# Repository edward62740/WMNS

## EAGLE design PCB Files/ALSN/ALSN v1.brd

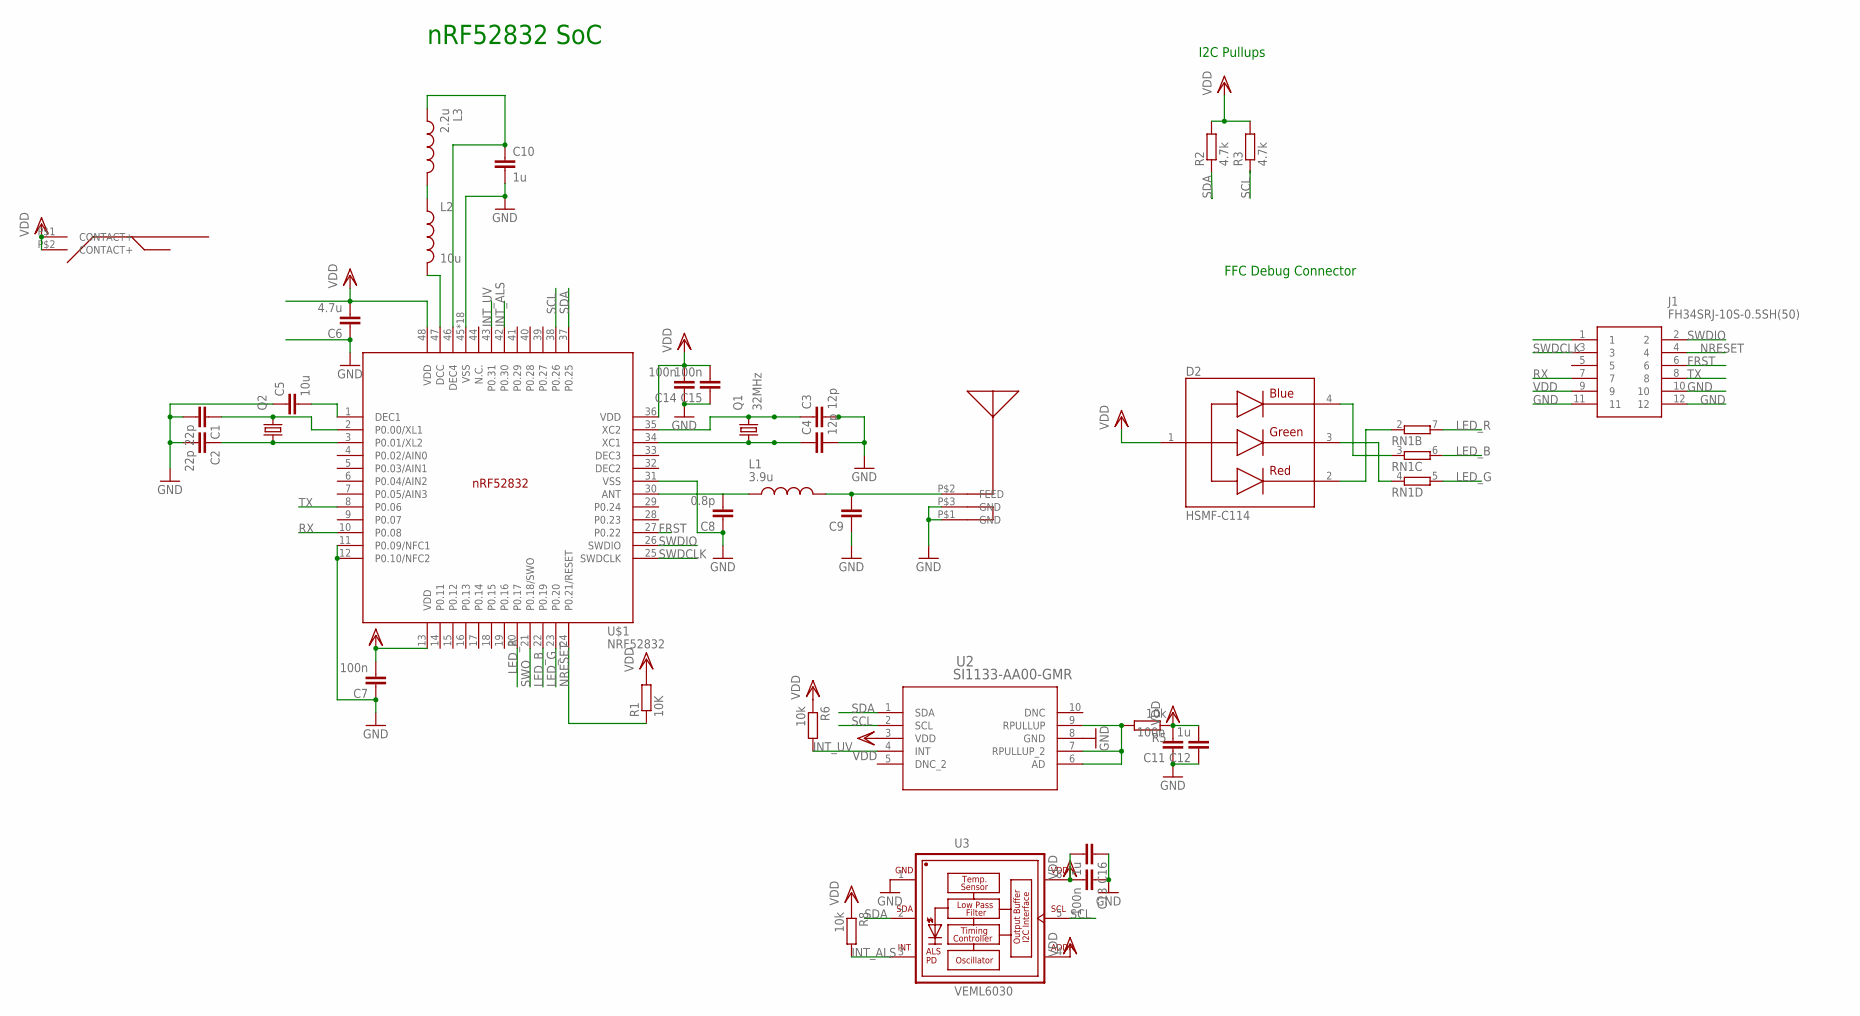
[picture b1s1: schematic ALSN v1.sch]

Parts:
C1, C2: 22p; C0402
C3, C4: 12p; C0402
C5: 10u; C0402
C6: 4.7u; C0402
C7: 100n; C0603R
C8: 0.8p; C0402
C9: 1.2p; C0402
C10, C12, C16: 1u; C0402
C11, C13, C14, C15: 100n; C0402
D2: HSMF-C114; DIOSC160X150X35-4N
J1: FH34SRJ-10S-0.5SH(50); FH34SRJ10S05SH50
L1: 3.9u; INDC0402X26N
L2: 10u; L0603
L3: 2.2u; INDC0402X26N
Q1: 32MHz; 2.0X1.6_KX-5
Q2: KX-327-RT; 2.0X1.2
R1: 10K; R0402
R2, R3: 4.7k; R0402
R5, R6, R8: 10k; R0402
RN1: 4R-N0402ARV341; 4X0402ARV341
U2: SI1133-AA00-GMR; 10QFN_2X2_SIL
U3: VEML6030; VISHAY_VEML6030_2X2X0.87
U$1: NRF52832; QFN40P600X600X90-48_N
U$2: CR2032-THT
U$4: CHIPANTENNAL2

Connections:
FRST: J1.6, U$1.27 (P0.22)
GND: C1.2, C2.2, C3.2, C4.2, C5.1, C6.1, C7.1, C8.1, C9.1, C10.2, C11.1, C12.1, C13.1, C14.1, C15.1, C16.1, J1.10, J1.11, J1.12, U2.8 (GND), U3.1 (GND), U$1.11 (P0.09/NFC1), U$1.12 (P0.10/NFC2), U$1.31 (VSS), U$1.45 (VSS), U$1.PAD (VSS), U$1.PAD@VIA01 (VSS), U$1.PAD@VIA02 (VSS), U$1.PAD@VIA03 (VSS), U$1.PAD@VIA04 (VSS), U$1.PAD@VIA05 (VSS), U$1.PAD@VIA06 (VSS), U$1.PAD@VIA07 (VSS), U$1.PAD@VIA08 (VSS), U$1.PAD@VIA09 (VSS), U$1.PAD@VIA10 (VSS), U$1.PAD@VIA11 (VSS), U$1.PAD@VIA12 (VSS), U$1.PAD@VIA13 (VSS), U$1.PAD@VIA14 (VSS), U$1.PAD@VIA15 (VSS), U$1.PAD@VIA16 (VSS), U$4.P$1 (GND), U$4.P$3 (GND)
INT_ALS: R8.2, U3.3 (INT), U$1.42 (P0.30)
INT_UV: R6.2, U2.4 (INT), U$1.43 (P0.31)
LED_B: RN1.6 (2), U$1.22 (P0.19)
LED_G: RN1.5 (2), U$1.23 (P0.20)
LED_R: RN1.7 (2), U$1.20 (P0.17)
unnamed: C1.1, Q2.2, U$1.2 (P0.00/XL1)
unnamed: C2.1, Q2.1, U$1.3 (P0.01/XL2)
unnamed: C3.1, Q1.3 (2), U$1.35 (XC2)
unnamed: C4.1, Q1.1, U$1.34 (XC1)
unnamed: C5.2, U$1.1 (DEC1)
unnamed: C8.2, L1.1, U$1.30 (ANT)
unnamed: L2.2, U$1.47 (DCC)
unnamed: L2.1, L3.2
unnamed: C10.1, L3.1, U$1.46 (DEC4)
unnamed: D2.3, RN1.4 (1)
unnamed: R5.2, U2.6 (AD), U2.7 (RPULLUP_2), U2.9 (RPULLUP)
unnamed: D2.2, RN1.2 (1)
unnamed: D2.4, RN1.3 (1)
NRESET: J1.4, R1.1, U$1.24 (P0.21/RESET)
RF: C9.2, L1.2, U$4.P$2 (FEED)
RX: J1.7, U$1.10 (P0.08)
SCL: R3.1, U2.2 (SCL), U3.5 (SCL), U$1.38 (P0.26)
SDA: R2.1, U2.1 (SDA), U3.2 (SDA), U$1.37 (P0.25)
SWDCLK: J1.3, U$1.25 (SWDCLK)
SWDIO: J1.2, U$1.26 (SWDIO)
SWO: U$1.21 (P0.18/SWO)
TX: J1.8, U$1.8 (P0.06)
VDD: C6.2, C7.2, C11.2, C12.2, C13.2, C14.2, C15.2, C16.2, D2.1, J1.9, R1.2, R2.2, R3.2, R5.1, R6.1, R8.1, U2.3 (VDD), U3.4 (ADDR), U3.6 (VDD), U$1.13 (VDD), U$1.36 (VDD), U$1.48 (VDD), U$2.P$1, U$2.P$2

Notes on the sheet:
nRF52832 SoC
I2C Pullups
FFC Debug Connector

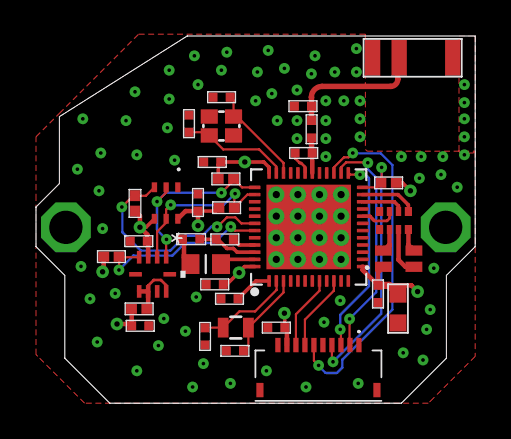
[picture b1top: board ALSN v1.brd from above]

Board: 4 copper layers, 24.4 x 20.4 mm, 35 parts (0 on the bottom side), 29 nets.

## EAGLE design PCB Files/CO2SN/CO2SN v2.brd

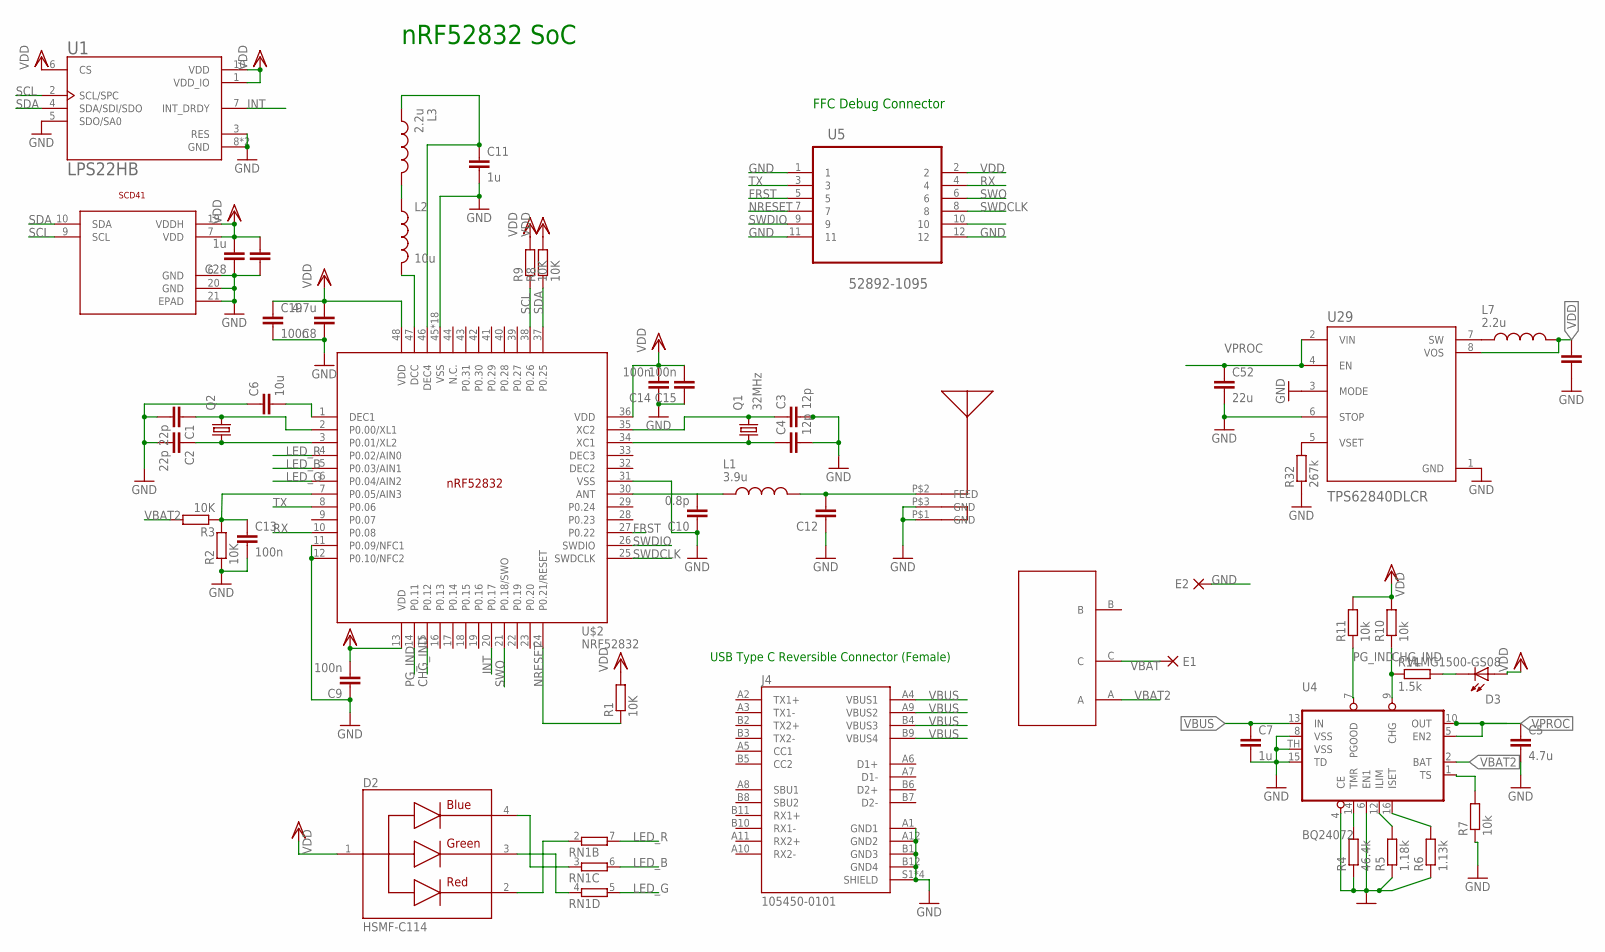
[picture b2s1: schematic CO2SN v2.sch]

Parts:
C1, C2: 22p; C0402
C3, C4: 12p; C0402
C5, C8: 4.7u; C0402
C6: 10u; C0402
C7, C11, C28: 1u; C0402
C9: 100n; C0603R
C10: 0.8p; C0402
C12: 1.2p; C0402
C13, C14, C15, C19: 100n; C0402
C29, C52, C58: 22u; C0603R
D2: HSMF-C114; DIOSC160X150X35-4N
D3: VLMG1500-GS08; LEDC1005X35N
E1, E2: DPADS_PAD-0400-S; DPADS_0400-S
J4: 105450-0101; MOLEX_105450-0101
L1: 3.9u; INDC0402X26N
L2: 10u; L0603
L3: 2.2u; INDC0402X26N
L7: 2.2u; INDC3225X120N
Q1: 32MHz; 2.0X1.6_KX-5
Q2: KX-327-RT; 2.0X1.2
R1, R2, R3, R8, R9: 10K; R0402
R4: 46.4k; R0402
R5: 1.18k; R0402
R6: 1.13k; R0402
R7, R10, R11: 10k; R0402
R14: 1.5k; R0402
R32: 267k; R0402
RN1: 4R-N0402ARV341; 4X0402ARV341
U1: LPS22HB; LGA10R50P2X3_200X200X80
U4: BQ24072; S-PVQFN-N16
U5: 52892-1095; MOLEX_52892-1095
U29: TPS62840DLCR; SON50P200X150X100-8N
U$1: SCD41
U$2: NRF52832; QFN40P600X600X90-48_N
U$3: SMDTOGGLESWITCH
U$4: CHIPANTENNAL2

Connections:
CHG_IND: R10.1, R14.1, U4.9 (CHG), U$2.15 (P0.12)
FRST: U5.5, U$2.27 (P0.22)
GND: C1.2, C2.2, C3.2, C4.2, C5.2, C6.1, C7.2, C8.1, C9.1, C10.1, C11.2, C12.1, C13.2, C14.1, C15.1, C19.2, C28.1, C29.2, C52.2, C58.2, E2.PAD, J4.A1 (GND1), J4.A12 (GND2), J4.B1 (GND3), J4.B12 (GND4), J4.S1 (SHIELD), J4.S2 (SHIELD), J4.S3 (SHIELD), J4.S4 (SHIELD), R2.1, R4.1, R5.1, R6.1, R7.1, R32.1, U1.3 (RES), U1.5 (SDO/SA0), U1.8 (GND), U1.9 (GND), U4.4 (CE), U4.6 (EN1), U4.8 (VSS), U4.15 (TD), U4.TH (VSS), U5.1, U5.11, U5.12, U29.1 (GND), U29.3 (MODE), U29.6 (STOP), U$1.6 (GND), U$1.20 (GND), U$1.21 (EPAD), U$2.11 (P0.09/NFC1), U$2.12 (P0.10/NFC2), U$2.31 (VSS), U$2.45 (VSS), U$2.PAD (VSS), U$2.PAD@VIA01 (VSS), U$2.PAD@VIA02 (VSS), U$2.PAD@VIA03 (VSS), U$2.PAD@VIA04 (VSS), U$2.PAD@VIA05 (VSS), U$2.PAD@VIA06 (VSS), U$2.PAD@VIA07 (VSS), U$2.PAD@VIA08 (VSS), U$2.PAD@VIA09 (VSS), U$2.PAD@VIA10 (VSS), U$2.PAD@VIA11 (VSS), U$2.PAD@VIA12 (VSS), U$2.PAD@VIA13 (VSS), U$2.PAD@VIA14 (VSS), U$2.PAD@VIA15 (VSS), U$2.PAD@VIA16 (VSS), U$4.P$1 (GND), U$4.P$3 (GND)
INT: U1.7 (INT_DRDY), U$2.20 (P0.17)
LED_B: RN1.6 (2), U$2.5 (P0.03/AIN1)
LED_G: RN1.5 (2), U$2.6 (P0.04/AIN2)
LED_R: RN1.7 (2), U$2.4 (P0.02/AIN0)
unnamed: C1.1, Q2.2, U$2.2 (P0.00/XL1)
unnamed: C2.1, Q2.1, U$2.3 (P0.01/XL2)
unnamed: C3.1, Q1.3 (2), U$2.35 (XC2)
unnamed: C4.1, Q1.1, U$2.34 (XC1)
unnamed: L2.2, U$2.47 (DCC)
unnamed: C10.2, L1.1, U$2.30 (ANT)
unnamed: C6.2, U$2.1 (DEC1)
unnamed: R4.2, U4.14 (TMR)
unnamed: R5.2, U4.12 (ILIM)
unnamed: L2.1, L3.2
unnamed: C11.1, L3.1, U$2.46 (DEC4)
unnamed: R6.2, U4.16 (ISET)
unnamed: D2.2, RN1.2 (1)
unnamed: D3.2, R14.2
unnamed: C13.1, R2.2, R3.1, U$2.7 (P0.05/AIN3)
unnamed: D2.3, RN1.4 (1)
unnamed: D2.4, RN1.3 (1)
unnamed: L7.1, U29.7 (SW)
unnamed: R32.2, U29.5 (VSET)
NRESET: R1.1, U5.7, U$2.24 (P0.21/RESET)
PG_IND: R11.1, U4.7 (PGOOD), U$2.14 (P0.11)
RF: C12.2, L1.2, U$4.P$2 (FEED)
RX: U5.4, U$2.10 (P0.08)
SCL: R9.1, U1.2 (SCL/SPC), U$1.9 (SCL), U$2.38 (P0.26)
SDA: R8.1, U1.4 (SDA/SDI/SDO), U$1.10 (SDA), U$2.37 (P0.25)
SWDCLK: U5.8, U$2.25 (SWDCLK)
SWDIO: U5.9, U$2.26 (SWDIO)
SWO: U5.6, U$2.21 (P0.18/SWO)
TS: R7.2, U4.1 (TS)
TX: U5.3, U$2.8 (P0.06)
VBAT: E1.PAD, U$3.C
VBAT2: R3.2, U4.2 (BAT), U$3.A
VBUS: C7.1, J4.A4 (VBUS1), J4.A9 (VBUS2), J4.B4 (VBUS3), J4.B9 (VBUS4), U4.13 (IN)
VDD: C8.2, C9.2, C14.2, C15.2, C19.1, C28.2, C29.1, C58.1, D2.1, D3.1, L7.2, R1.2, R8.2, R9.2, R10.2, R11.2, U1.1 (VDD_IO), U1.6 (CS), U1.10 (VDD), U5.2, U29.8 (VOS), U$1.7 (VDD), U$1.19 (VDDH), U$2.13 (VDD), U$2.36 (VDD), U$2.48 (VDD)
VPROC: C5.1, C52.1, U4.5 (EN2), U4.10 (OUT), U29.2 (VIN), U29.4 (EN)

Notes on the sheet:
nRF52832 SoC
USB Type C Reversible Connector (Female)
FFC Debug Connector

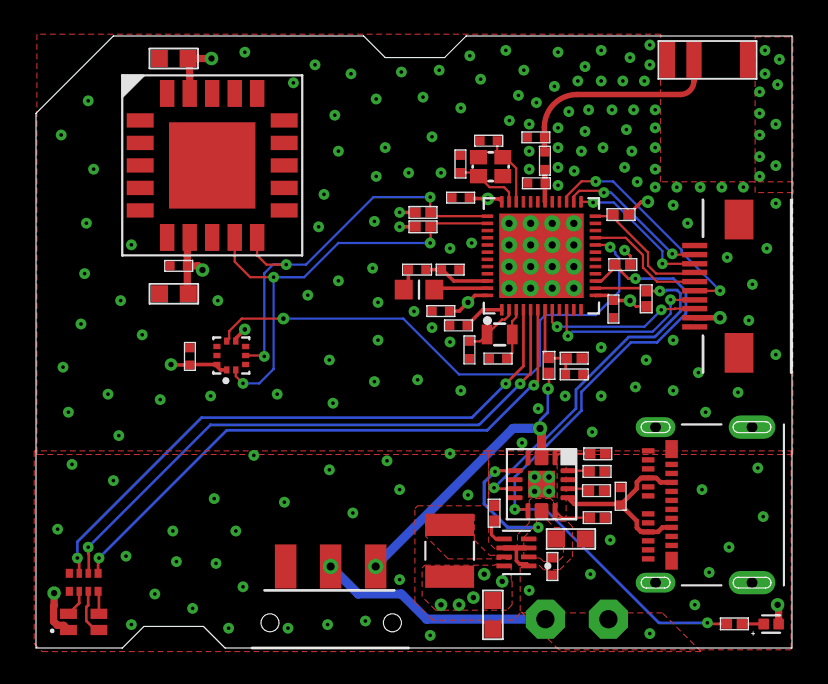
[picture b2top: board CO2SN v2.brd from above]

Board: 4 copper layers, 42.0 x 34.0 mm, 53 parts (0 on the bottom side), 42 nets.

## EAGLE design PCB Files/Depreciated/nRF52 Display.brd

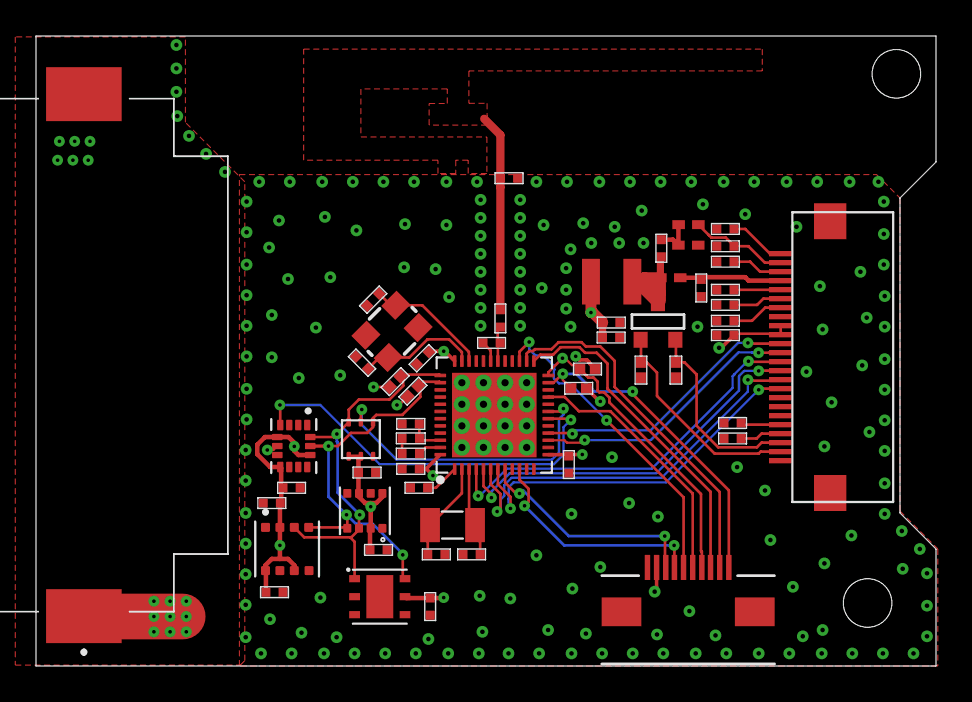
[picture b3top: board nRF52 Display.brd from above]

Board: 4 copper layers, 50.0 x 35.0 mm, 55 parts (0 on the bottom side), 43 nets.

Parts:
C1, C2: 12pF; C0402
C3, C4: 12p; C0402
C5: 10u; C0402
C6, C26, C27: 4.7u; C0402
C7, C11, C12, C13, C17, C30: 100n; C0402
C8: 0.8p; C0402
C9: 1.2p; C0402
C10, C15, C16, C18, C19, C20, C21, C22, C23, C24, C25, C28, C29: 1u; C0402
C14: 100u; C0402
D1, D2, D3: 1PS79SB30,115; SOD523
K1: 687124149022
L1: 3.9u; INDC0402X26N
L2: SM-NE29
L4: 10u; INDC0402X26N
L5: 15n; INDC0402X26N
R1, R4: 10K; R0402
R2, R3: 4.7k; R0402
R5: 10k; R0402
R6: 0.47; R0402
T1: SOT-23
U1: CR2032-BS-6-1; CR2032BS61
U2: BME280; PSON65P250X250X100-8N
U4: SHT20; DFN300X300X110-7N
U5: 52892-1095; MOLEX_52892-1095
U6: BME680; PSON80P300X300X100-8N
U7: BMI160; PQFN50P300X250X88-14N
U$1: NRF52832; QFN40P600X600X90-48_N
U$2: TI-OPT3001
X1: ABS07-32.768KHZ-T
Y1: CRYSTAL-26MHZSMD-3.2X2.5; CRYSTAL-SMD-3.2X2.5MM

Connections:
BUSY: K1.9, U$1.7
CS: K1.12, U$1.4
D/C: K1.11, U$1.5
DFU: R4.1, U5.10, U$1.23
FRST: U5.5, U$1.27
GDR: K1.2, R5.2, T1.3
GND: C1.2, C2.2, C3.2, C4.2, C5.1, C6.1, C7.1, C8.1, C9.1, C10.2, C11.1, C12.1, C13.1, C14.1, C15.1, C16.1, C17.2, C18.1, C19.1, C20.1, C21.1, C22.2, C23.1, C24.1, C25.1, C26.2, C28.2, C29.2, C30.2, D2.1, K1.8, K1.17, R5.1, R6.1, U1.2, U2.1, U2.5, U2.7, U4.2, U4.7, U5.1, U5.11, U5.12, U6.1, U6.5, U6.7, U7.1, U7.6, U7.7, U$1.11, U$1.12, U$1.31, U$1.45, U$1.PAD, U$1.PAD@VIA01, U$1.PAD@VIA02, U$1.PAD@VIA03, U$1.PAD@VIA04, U$1.PAD@VIA05, U$1.PAD@VIA06, U$1.PAD@VIA07, U$1.PAD@VIA08, U$1.PAD@VIA09, U$1.PAD@VIA10, U$1.PAD@VIA11, U$1.PAD@VIA12, U$1.PAD@VIA13, U$1.PAD@VIA14, U$1.PAD@VIA15, U$1.PAD@VIA16, U$2.3
INT_BMI: U7.4, U$1.18
INT_OPT: U$1.19, U$2.5
MOSI: K1.14, U$1.16
unnamed: C1.1, U$1.2, X1.2
unnamed: C2.1, U$1.3, X1.1
unnamed: C3.1, U$1.35, Y1.3
unnamed: C4.1, U$1.34, Y1.1
unnamed: C5.2, U$1.1
unnamed: C8.2, L1.1, U$1.30
unnamed: C27.2, D3.2, L2.2, T1.1
unnamed: C21.2, K1.18
unnamed: L4.2, U$1.47
unnamed: L4.1, L5.2
unnamed: C10.1, L5.1, U$1.46
unnamed: C18.2, K1.22
unnamed: C20.2, K1.19
unnamed: C19.2, K1.20
unnamed: C15.2, K1.24
unnamed: C24.2, K1.4
unnamed: C25.2, K1.5
unnamed: C27.1, D1.1, D2.2
NRESET: R1.1, U5.7, U$1.24
PREVGH: C22.1, D3.1, K1.21
PREVGL: C16.2, D1.2, K1.23
RES: K1.10, U$1.6
RESE: K1.3, R6.2, T1.2
RF: C9.2, L1.2
RX: U5.4, U$1.10
SCK: K1.13, U$1.15
SCL: R3.1, U2.4, U4.6, U6.4, U7.13, U$1.38, U$2.4
SDA: R2.1, U2.3, U4.1, U6.3, U7.14, U$1.37, U$2.6
SWDCLK: U5.8, U$1.25
SWDIO: U5.9, U$1.26
SWO: U5.6, U$1.21
TX: U5.3, U$1.8
VDD: C6.2, C7.2, C11.2, C12.2, C13.2, C14.2, C17.1, C23.2, C26.1, C28.1, C29.1, C30.1, K1.15, K1.16, L2.1, R1.2, R2.2, R3.2, R4.2, U1.1, U2.2, U2.6, U2.8, U4.5, U5.2, U6.2, U6.6, U6.8, U7.5, U7.8, U7.12, U$1.13, U$1.36, U$1.48, U$2.1, U$2.2

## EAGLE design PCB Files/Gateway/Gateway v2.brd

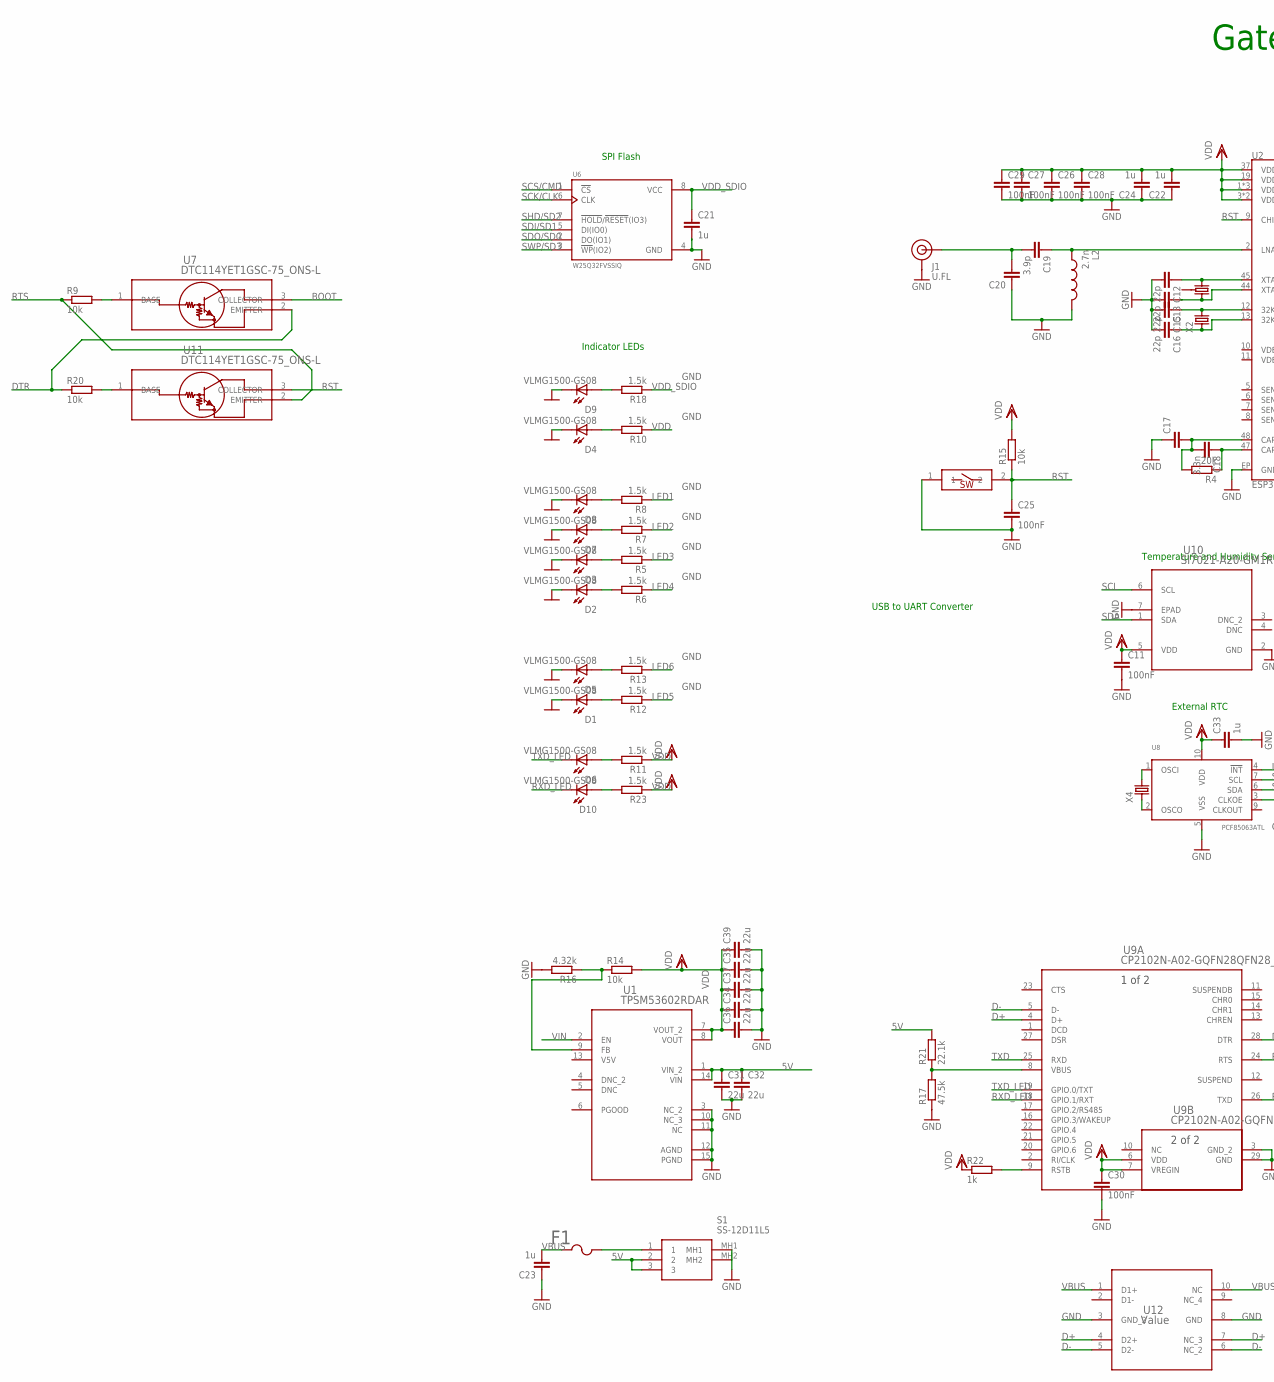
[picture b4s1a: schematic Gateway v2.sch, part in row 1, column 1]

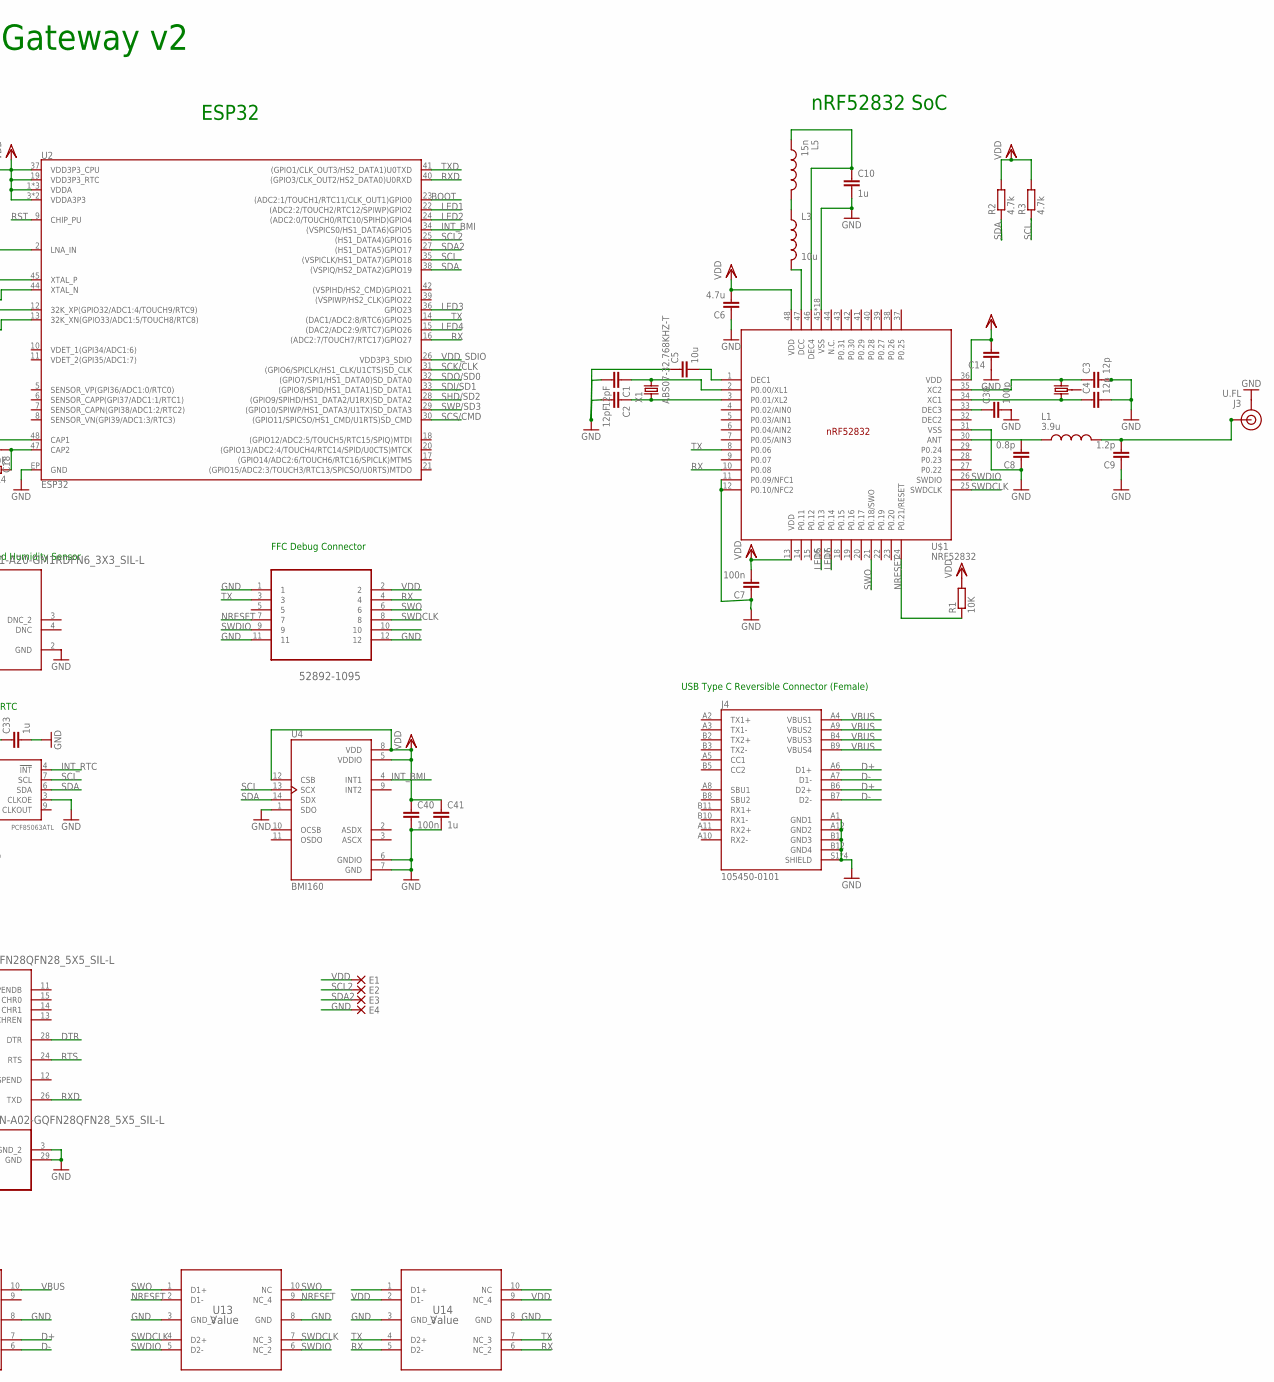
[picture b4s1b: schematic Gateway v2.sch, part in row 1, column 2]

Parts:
C1, C2: 12pF; C0402
C3, C4: 12p; C0402
C5: 10u; C0402
C6: 4.7u; C0402
C7, C40: 100n; C0402
C8: 0.8p; C0402
C9: 1.2p; C0402
C10, C21, C41: 1u; C0402
C11, C25, C26, C27, C28, C29, C30: 100nF; C0402
C12, C13, C15, C16: 22p; C0402
C14: 100u; C0402
C17: 10n; C0402
C18: 3.3n; C0402
C19: 3.9p; C0402
C20: 2.4p; C0402
C22, C23, C24, C33: 1u; C0603R
C31, C32, C34, C35, C36, C37, C39: 22u; C0603R
C38: 100p; C0402
D1, D2, D3, D4, D5, D6, D7, D8, D9, D10: VLMG1500-GS08; LEDC1005X35N
E1, E2, E3, E4: DPADS_PAD-0400-S; DPADS_0400-S
F1: 1210L050YR1210LSERIES_LTF-L; 1210LSERIES_LTF-L
J1, J3: U.FL
J4: 105450-0101; MOLEX_105450-0101
L1: 3.9u; INDC0402X26N
L2: 2.7n; INDC0402X26N
L3: 10u; L0603
L5: 15n; INDC0402X26N
R1: 10K; R0402
R2, R3: 4.7k; R0402
R4: 20k; R0402
R5, R6, R7, R8, R10, R11, R12, R13, R18, R23: 1.5k; R0402
R9, R14, R15, R20: 10k; R0402
R16: 4.32k; R0402
R17: 47.5k; R0402
R21: 22.1k; R0402
R22: 1k; R0402
RESET: SMDSWITCH; RESC4217X170
S1: SS-12D11L5; SS12D11L5
U1: TPSM53602RDAR; B3QFN15_RDA_TEX
U2: ESP32; QFN48-0.4MM
U4: BMI160; PQFN50P300X250X88-14N
U5: 52892-1095; MOLEX_52892-1095
U6: W25Q32FVSSIQ; SOIC127P790X216-8N
U7, U11: DTC114YET1GSC-75_ONS-L; SC-75_ONS-L
U8: PCF85063ATL; SOT1197-1
U9: CP2102N-A02-GQFN28QFN28_5X5_SIL-L; QFN28_5X5_SIL-L
U10: SI7021-A20-GM1RDFN6_3X3_SIL-L; DFN6_3X3_SIL-L
U12, U13, U14: Value; DQA0010A
U$1: NRF52832; QFN40P600X600X90-48_N
X1, X2, X4: ABS07-32.768KHZ-T
Y1, Y2: CRYSTAL-26MHZSMD-3.2X2.5; CRYSTAL-SMD-3.2X2.5MM

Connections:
5V: C31.1, C32.1, R21.2, S1.2, S1.3, U1.1 (VIN_2), U1.14 (VIN)
BOOT: U2.23 ((ADC2:1/TOUCH1/RTC11/CLK_OUT1)GPIO0), U7.3 (COLLECTOR)
D+: J4.A6 (D1+), J4.B6 (D2+), U9.4 (D+), U12.4 (D2+), U12.7 (NC_3)
D-: J4.A7 (D1-), J4.B7 (D2-), U9.5 (D-), U12.5 (D2-), U12.6 (NC_2)
DTR: R20.1, U7.2 (EMITTER), U9.28 (DTR)
GND: C1.2, C2.2, C3.2, C4.2, C5.1, C6.1, C7.1, C8.1, C9.1, C10.2, C11.2, C12.2, C13.2, C14.1, C15.2, C16.2, C17.1, C20.1, C21.2, C22.1, C23.1, C24.1, C25.2, C26.2, C27.2, C28.2, C29.2, C30.2, C31.2, C32.2, C33.2, C34.2, C35.2, C36.2, C37.2, C38.2, C39.2, C40.2, C41.2, D1.2, D2.2, D3.2, D4.2, D5.2, D7.2, D8.2, D9.2, E4.PAD, J1.1 (GND), J1.2 (GND), J3.1 (GND), J3.2 (GND), J4.A1 (GND1), J4.A12 (GND2), J4.B1 (GND3), J4.B12 (GND4), J4.S1 (SHIELD), J4.S2 (SHIELD), J4.S3 (SHIELD), J4.S4 (SHIELD), L2.2, R16.2, R17.1, RESET.1, S1.MH1, S1.MH2, U1.3 (NC_2), U1.10 (NC_3), U1.11 (NC), U1.12 (AGND), U1.15 (PGND), U2.EP (GND), U4.1 (SDO), U4.6 (GNDIO), U4.7 (GND), U5.1, U5.11, U5.12, U6.4 (GND), U8.3 (CLKOE), U8.5 (VSS), U9.3 (GND_2), U9.29 (GND), U10.2 (GND), U10.7 (EPAD), U12.3 (GND_2), U12.8 (GND), U13.3 (GND_2), U13.8 (GND), U14.3 (GND_2), U14.8 (GND), U$1.11 (P0.09/NFC1), U$1.12 (P0.10/NFC2), U$1.31 (VSS), U$1.45 (VSS), U$1.PAD (VSS), U$1.PAD@VIA01 (VSS), U$1.PAD@VIA02 (VSS), U$1.PAD@VIA03 (VSS), U$1.PAD@VIA04 (VSS), U$1.PAD@VIA05 (VSS), U$1.PAD@VIA06 (VSS), U$1.PAD@VIA07 (VSS), U$1.PAD@VIA08 (VSS), U$1.PAD@VIA09 (VSS), U$1.PAD@VIA10 (VSS), U$1.PAD@VIA11 (VSS), U$1.PAD@VIA12 (VSS), U$1.PAD@VIA13 (VSS), U$1.PAD@VIA14 (VSS), U$1.PAD@VIA15 (VSS), U$1.PAD@VIA16 (VSS)
INT_BMI: U2.34 ((VSPICS0/HS1_DATA6)GPIO5), U4.4 (INT1)
INT_RTC: U8.4 (!INT!)
LED1: R8.1, U2.22 ((ADC2:2/TOUCH2/RTC12/SPIWP)GPIO2)
LED2: R7.1, U2.24 ((ADC2:0/TOUCH0/RTC10/SPIHD)GPIO4)
LED3: R5.1, U2.36 (GPIO23)
LED4: R6.1, U2.15 ((DAC2/ADC2:9/RTC7)GPIO26)
LED5: R12.1, U$1.16 (P0.13)
LED6: R13.1, U$1.17 (P0.14)
unnamed: C1.1, U$1.2 (P0.00/XL1), X1.2
unnamed: C2.1, U$1.3 (P0.01/XL2), X1.1
unnamed: C3.1, U$1.35 (XC2), Y1.3 (2)
unnamed: C4.1, U$1.34 (XC1), Y1.1
unnamed: C5.2, U$1.1 (DEC1)
unnamed: C8.2, L1.1, U$1.30 (ANT)
unnamed: C13.1, U2.44 (XTAL_N), Y2.3 (2)
unnamed: C12.1, U2.45 (XTAL_P), Y2.1
unnamed: L3.2, U$1.47 (DCC)
unnamed: L3.1, L5.2
unnamed: C10.1, L5.1, U$1.46 (DEC4)
unnamed: C15.1, U2.12 (32K_XP(GPIO32/ADC1:4/TOUCH9/RTC9)), X2.2
unnamed: C16.1, U2.13 (32K_XN(GPIO33/ADC1:5/TOUCH8/RTC8)), X2.1
unnamed: C18.1, R4.1, U2.47 (CAP2)
unnamed: C38.1, U$1.33 (DEC3)
unnamed: C17.2, C18.2, R4.2, U2.48 (CAP1)
unnamed: D3.1, R5.2
unnamed: D7.1, R7.2
unnamed: D8.1, R8.2
unnamed: C19.1, L2.1, U2.2 (LNA_IN)
unnamed: R17.2, R21.1, U9.8 (VBUS)
unnamed: D2.1, R6.2
unnamed: D4.1, R10.2
unnamed: D1.1, R12.2
unnamed: D5.1, R13.2
unnamed: C19.2, C20.2, J1.FEED (SIGNAL)
unnamed: R20.2, U11.1 (BASE)
unnamed: R9.2, U7.1 (BASE)
unnamed: D9.1, R18.2
unnamed: R14.1, R16.1, U1.9 (FB)
unnamed: U8.1 (OSCI), X4.2
unnamed: U8.2 (OSCO), X4.1
unnamed: R22.2, U9.9 (RSTB)
unnamed: D6.1, R11.2
unnamed: D10.1, R23.2
unnamed: F1.2, S1.1
NRESET: R1.1, U5.7, U13.2 (D1-), U13.9 (NC_4), U$1.24 (P0.21/RESET)
RFP1: C9.2, J3.FEED (SIGNAL), L1.2
RST: C25.1, R15.1, RESET.2, U2.9 (CHIP_PU), U11.3 (COLLECTOR)
RTS: R9.1, U9.24 (RTS), U11.2 (EMITTER)
RX: U2.16 ((ADC2:7/TOUCH7/RTC17)GPIO27), U5.4, U14.5 (D2-), U14.6 (NC_2), U$1.10 (P0.08)
RXD: U2.40 ((GPIO3/CLK_OUT2/HS2_DATA0)U0RXD), U9.26 (TXD)
RXD_LED: D10.2, U9.18 (GPIO.1/RXT)
SCK/CLK: U2.31 ((GPIO6/SPICLK/HS1_CLK/U1CTS)SD_CLK), U6.6 (CLK)
SCL: R3.1, U2.35 ((VSPICLK/HS1_DATA7)GPIO18), U4.13 (SCX), U8.7 (SCL), U10.6 (SCL)
SCL2: E2.PAD, U2.25 ((HS1_DATA4)GPIO16)
SCS/CMD: U2.30 ((GPIO11/SPICSO/HS1_CMD/U1RTS)SD_CMD), U6.1 (!CS)
SDA: R2.1, U2.38 ((VSPIQ/HS2_DATA2)GPIO19), U4.14 (SDX), U8.6 (SDA), U10.1 (SDA)
SDA2: E3.PAD, U2.27 ((HS1_DATA5)GPIO17)
SDI/SD1: U2.33 ((GPIO8/SPID/HS1_DATA1)SD_DATA1), U6.5 (DI(IO0))
SDO/SD0: U2.32 ((GPIO7/SPI1/HS1_DATA0)SD_DATA0), U6.2 (DO(IO1))
SHD/SD2: U2.28 ((GPIO9/SPIHD/HS1_DATA2/U1RX)SD_DATA2), U6.7 (!HOLD!/!RESET!(IO3))
SWDCLK: U5.8, U13.4 (D2+), U13.7 (NC_3), U$1.25 (SWDCLK)
SWDCLK1: U14.1 (D1+)
SWDIO: U5.9, U13.5 (D2-), U13.6 (NC_2), U$1.26 (SWDIO)
SWO: U5.6, U13.1 (D1+), U13.10 (NC), U$1.21 (P0.18/SWO)
SWP/SD3: U2.29 ((GPIO10/SPIWP/HS1_DATA3/U1TX)SD_DATA3), U6.3 (!WP!(IO2))
TX: U2.14 ((DAC1/ADC2:8/RTC6)GPIO25), U5.3, U14.4 (D2+), U14.7 (NC_3), U$1.8 (P0.06)
TXD: U2.41 ((GPIO1/CLK_OUT3/HS2_DATA1)U0TXD), U9.25 (RXD)
TXD_LED: D6.2, U9.19 (GPIO.0/TXT)
VBUS: C23.2, F1.1, J4.A4 (VBUS1), J4.A9 (VBUS2), J4.B4 (VBUS3), J4.B9 (VBUS4), U12.1 (D1+), U12.10 (NC)
VDD: C6.2, C7.2, C11.1, C14.2, C22.2, C24.2, C26.1, C27.1, C28.1, C29.1, C30.1, C33.1, C34.1, C35.1, C36.1, C37.1, C39.1, C40.1, C41.1, E1.PAD, R1.2, R2.2, R3.2, R10.1, R11.1, R14.2, R15.2, R22.1, R23.1, U1.7 (VOUT_2), U1.8 (VOUT), U2.1 (VDDA), U2.3 (VDDA3P3), U2.4 (VDDA3P3), U2.19 (VDD3P3_RTC), U2.37 (VDD3P3_CPU), U2.43 (VDDA), U2.46 (VDDA), U4.5 (VDDIO), U4.8 (VDD), U4.12 (CSB), U5.2, U8.10 (VDD), U9.6 (VDD), U9.7 (VREGIN), U10.5 (VDD), U14.2 (D1-), U14.9 (NC_4), U$1.13 (VDD), U$1.36 (VDD), U$1.48 (VDD)
VDD_SDIO: C21.1, R18.1, U2.26 (VDD3P3_SDIO), U6.8 (VCC)
VIN: U1.2 (EN)

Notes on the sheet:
Indicator LEDs
SPI Flash
USB to UART Converter
External RTC
Temperature and Humidity Sensor
FFC Debug Connector
USB Type C Reversible Connector (Female)
nRF52832 SoC
ESP32
Gateway v2

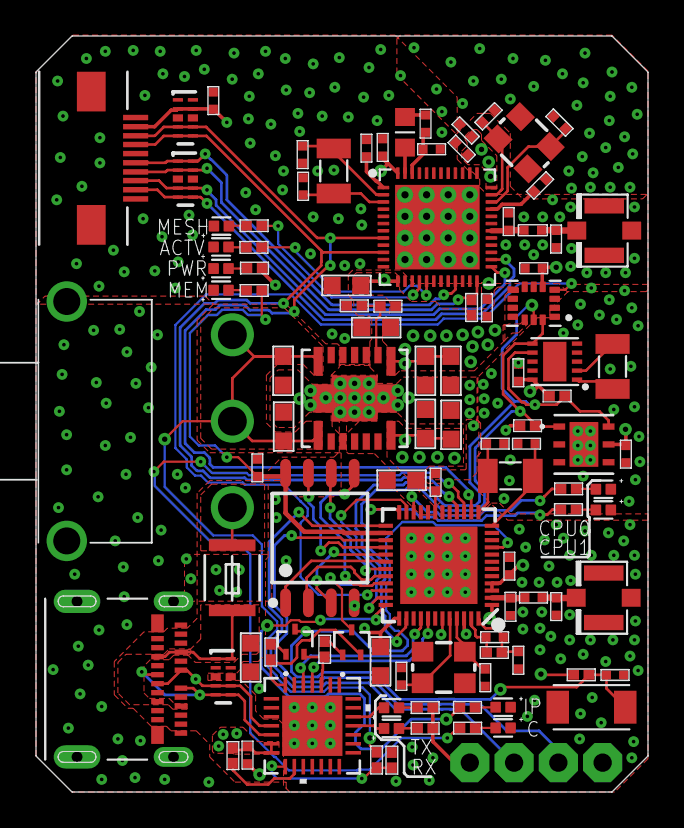
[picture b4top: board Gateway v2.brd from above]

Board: 4 copper layers, 34.0 x 42.0 mm, 106 parts (0 on the bottom side), 75 nets.

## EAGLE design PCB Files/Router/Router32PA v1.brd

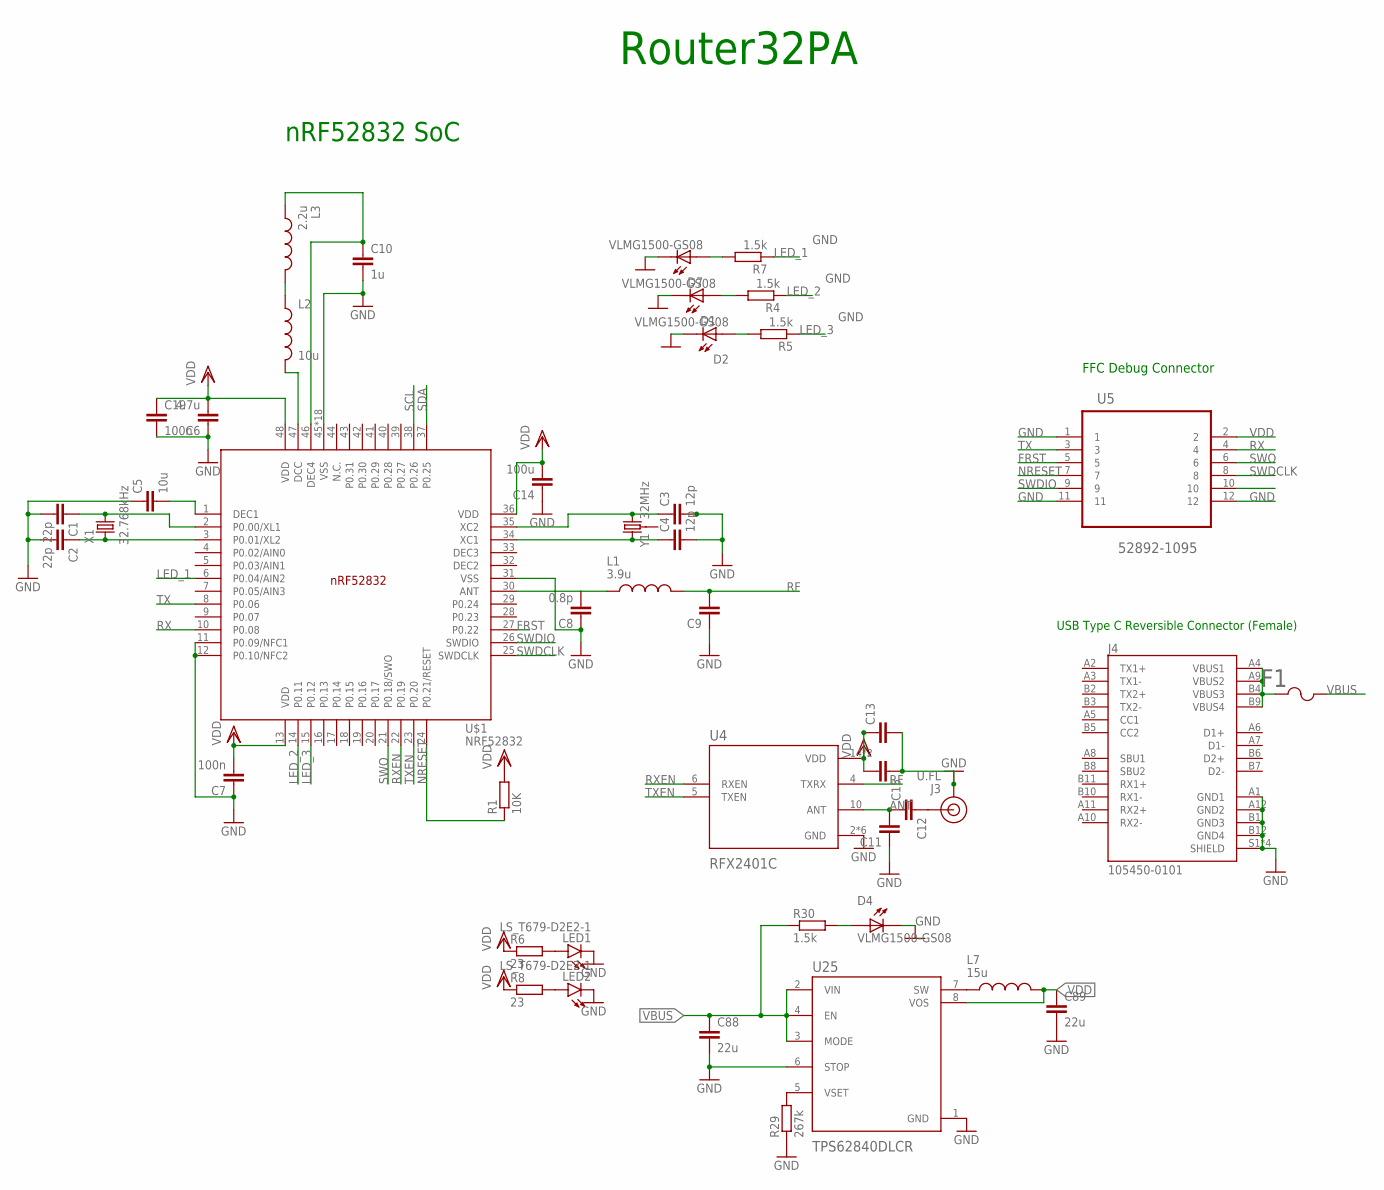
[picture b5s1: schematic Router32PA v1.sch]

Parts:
C1, C2: 22p; C0402
C3, C4: 12p; C0402
C5: 10u; C0402
C6: 4.7u; C0402
C7: 100n; C0603R
C8: 0.8p; C0402
C9, C11, C12, C13, C15: 1.2p; C0402
C10: 1u; C0402
C14: 100u; C0402
C19: 100n; C0402
C88, C89: 22u; C0603R
D1, D2, D4, D7: VLMG1500-GS08; LEDC1005X35N
F1: 1210L050YR1210LSERIES_LTF-L; 1210LSERIES_LTF-L
J3: U.FL
J4: 105450-0101; MOLEX_105450-0101
L1: 3.9u; INDC0402X26N
L2: 10u; L0603
L3: 2.2u; INDC0402X26N
L7: 15u; INDC3225X120N
LED1, LED2: LS_T679-D2E2-1; PLCC2
R1: 10K; R0402
R4, R5, R7, R30: 1.5k; R0402
R6, R8: 23; R0402
R29: 267k; R0402
U4: RFX2401C; QFN50P300X300X60-17N
U5: 52892-1095; MOLEX_52892-1095
U25: TPS62840DLCR; SON50P200X150X100-8N
U$1: NRF52832; QFN40P600X600X90-48_N
X1: 32.768kHz; ABS07-32.768KHZ-T
Y1: 32MHz; CRYSTAL-SMD-3.2X2.5MM

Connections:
ANT: C11.2, C12.2, U4.10 (ANT)
FRST: U5.5, U$1.27 (P0.22)
GND: C1.2, C2.2, C3.2, C4.2, C5.1, C6.1, C7.1, C8.1, C9.1, C10.2, C11.1, C13.2, C14.1, C15.1, C19.2, C88.2, C89.2, D1.2, D2.2, D4.2, D7.2, J3.1 (GND), J3.2 (GND), J4.A1 (GND1), J4.A12 (GND2), J4.B1 (GND3), J4.B12 (GND4), J4.S1 (SHIELD), J4.S2 (SHIELD), J4.S3 (SHIELD), J4.S4 (SHIELD), LED1.C, LED2.C, R29.1, U4.2 (GND), U4.3 (GND), U4.8 (GND), U4.9 (GND), U4.11 (GND), U4.17 (GND), U5.1, U5.11, U5.12, U25.1 (GND), U25.6 (STOP), U$1.11 (P0.09/NFC1), U$1.12 (P0.10/NFC2), U$1.31 (VSS), U$1.45 (VSS), U$1.PAD (VSS), U$1.PAD@VIA01 (VSS), U$1.PAD@VIA02 (VSS), U$1.PAD@VIA03 (VSS), U$1.PAD@VIA04 (VSS), U$1.PAD@VIA05 (VSS), U$1.PAD@VIA06 (VSS), U$1.PAD@VIA07 (VSS), U$1.PAD@VIA08 (VSS), U$1.PAD@VIA09 (VSS), U$1.PAD@VIA10 (VSS), U$1.PAD@VIA11 (VSS), U$1.PAD@VIA12 (VSS), U$1.PAD@VIA13 (VSS), U$1.PAD@VIA14 (VSS), U$1.PAD@VIA15 (VSS), U$1.PAD@VIA16 (VSS)
LED_1: R7.1, U$1.6 (P0.04/AIN2)
LED_2: R4.1, U$1.14 (P0.11)
LED_3: R5.1, U$1.15 (P0.12)
unnamed: C1.1, U$1.2 (P0.00/XL1), X1.2
unnamed: C2.1, U$1.3 (P0.01/XL2), X1.1
unnamed: C3.1, U$1.35 (XC2), Y1.3 (2)
unnamed: C4.1, U$1.34 (XC1), Y1.1
unnamed: C5.2, U$1.1 (DEC1)
unnamed: C8.2, L1.1, U$1.30 (ANT)
unnamed: D1.1, R4.2
unnamed: D2.1, R5.2
unnamed: L2.2, U$1.47 (DCC)
unnamed: L2.1, L3.2
unnamed: C10.1, L3.1, U$1.46 (DEC4)
unnamed: F1.1, J4.A4 (VBUS1), J4.A9 (VBUS2), J4.B4 (VBUS3), J4.B9 (VBUS4)
unnamed: LED1.A, R6.2
unnamed: LED2.A, R8.2
unnamed: C12.1, J3.FEED (SIGNAL)
unnamed: D7.1, R7.2
unnamed: L7.1, U25.7 (SW)
unnamed: R29.2, U25.5 (VSET)
unnamed: D4.1, R30.2
NRESET: R1.1, U5.7, U$1.24 (P0.21/RESET)
RF: C9.2, L1.2, U4.4 (TXRX)
RX: U5.4, U$1.10 (P0.08)
RXEN: U4.6 (RXEN), U$1.22 (P0.19)
SCL: U$1.38 (P0.26)
SDA: U$1.37 (P0.25)
SWDCLK: U5.8, U$1.25 (SWDCLK)
SWDIO: U5.9, U$1.26 (SWDIO)
SWO: U5.6, U$1.21 (P0.18/SWO)
TX: U5.3, U$1.8 (P0.06)
TXEN: U4.5 (TXEN), U$1.23 (P0.20)
VBUS: C88.1, F1.2, R30.1, U25.2 (VIN), U25.3 (MODE), U25.4 (EN)
VDD: C6.2, C7.2, C13.1, C14.2, C15.2, C19.1, C89.1, L7.2, R1.2, R6.1, R8.1, U4.14 (VDD), U4.16 (VDD), U5.2, U25.8 (VOS), U$1.13 (VDD), U$1.36 (VDD), U$1.48 (VDD)

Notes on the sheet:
nRF52832 SoC
FFC Debug Connector
Router32PA
USB Type C Reversible Connector (Female)

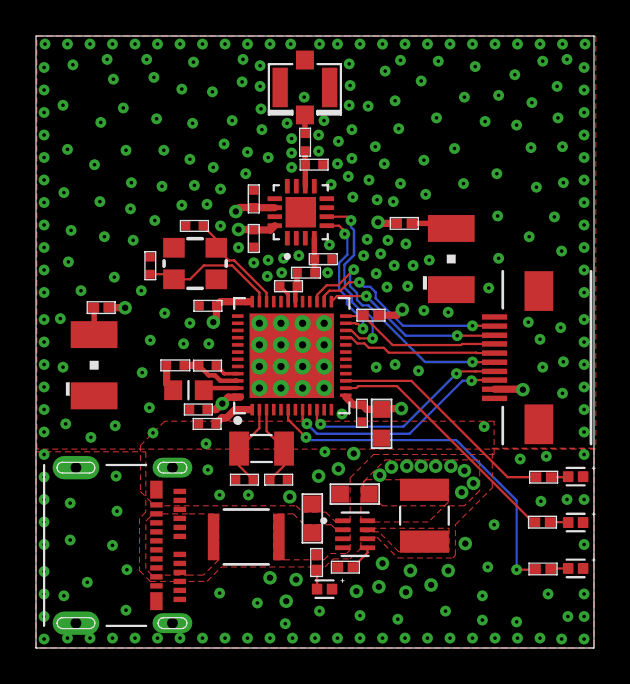
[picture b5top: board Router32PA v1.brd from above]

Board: 4 copper layers, 31.0 x 34.0 mm, 45 parts (0 on the bottom side), 36 nets.

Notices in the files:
parts and their libraries:
crystal-geyer_V1_0: Copyright: Geyer-Electronic
COPYRIGHT: Copyright (C) 2018 Accelerated Designs. All rights reserved
FaBo-Mems: Released under the Creative Commons Attribution-ShareAlike 4.0 License
https://creativecommons.org/licenses/by-sa/4.0
